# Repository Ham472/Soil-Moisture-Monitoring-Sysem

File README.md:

# Soil-Moisture-Monitoring-Sysem

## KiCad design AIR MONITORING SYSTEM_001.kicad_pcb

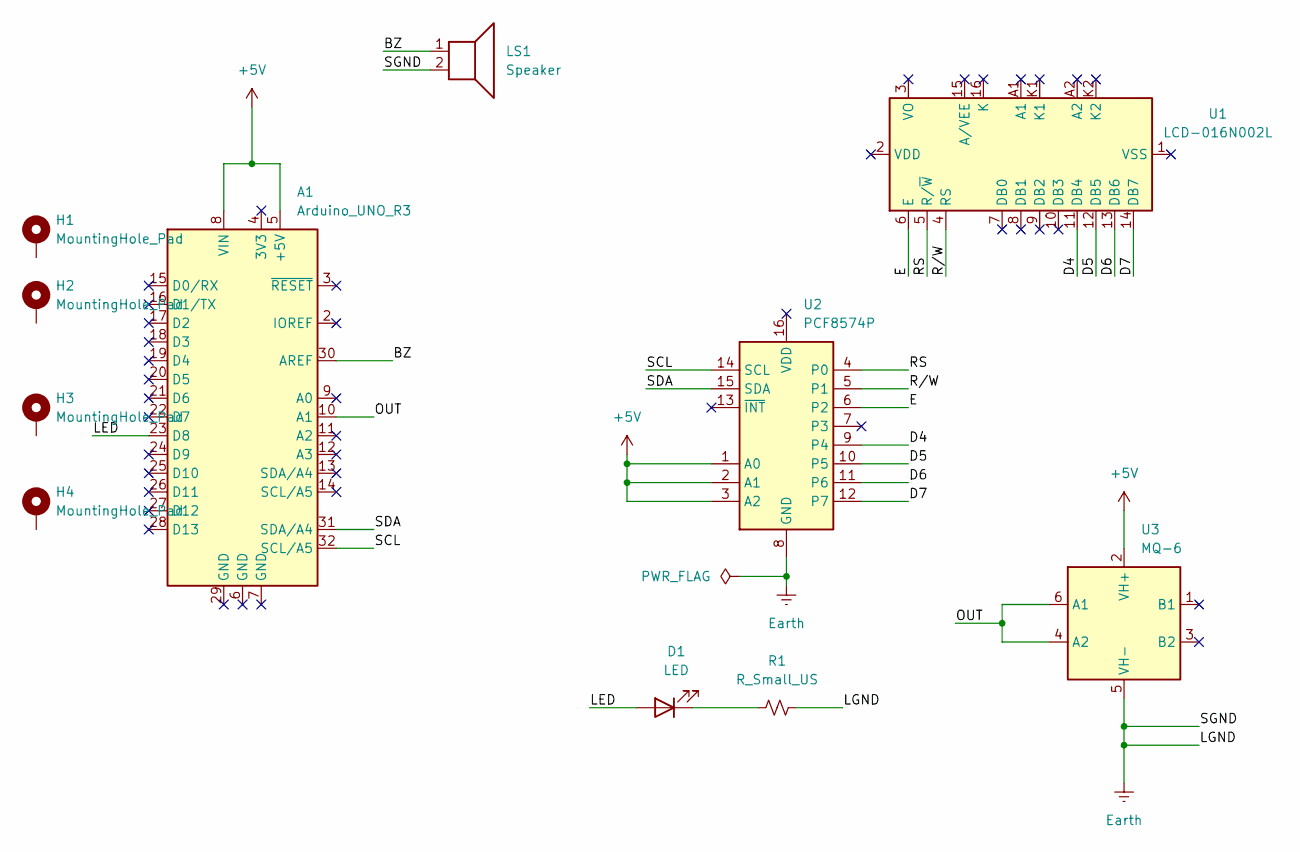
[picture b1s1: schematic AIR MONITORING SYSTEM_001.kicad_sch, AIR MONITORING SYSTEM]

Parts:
A1: Arduino_UNO_R3
D1: LED; LED_D3.0mm_Clear
H1, H2, H3, H4: MountingHole_Pad; MountingHole_2.5mm_Pad
LS1: Speaker; Reverb_BTDR-1H
R1: R_Small_US; R_Axial_DIN0411_L9.9mm_D3.6mm_P7.62mm_Vertical
U1: LCD-016N002L
U2: PCF8574P; DIP-16_W7.62mm
U3: MQ-6

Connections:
+5V: A1.5 (+5V), A1.8 (VIN), U2.1 (A0), U2.2 (A1), U2.3 (A2), U3.2 (VH+)
/BZ: A1.30 (AREF), LS1.1
/D4: U1.11 (DB4), U2.9 (P4)
/D5: U1.12 (DB5), U2.10 (P5)
/D6: U1.13 (DB6), U2.11 (P6)
/D7: U1.14 (DB7), U2.12 (P7)
/E: U1.6 (E), U2.6 (P2)
/LED: A1.23 (D8), D1.2 (A)
/OUT: A1.10 (A1), U3.4 (A2), U3.6 (A1)
/RS: U1.5 (R/~W), U2.4 (P0)
/R/W: U1.4 (RS), U2.5 (P1)
/SCL: A1.32 (SCL/A5), U2.14 (SCL)
/SDA: A1.31 (SDA/A4), U2.15 (SDA)
Earth: LS1.2, R1.2, U2.8 (GND), U3.5 (VH-)
unnamed: D1.1 (K), R1.1

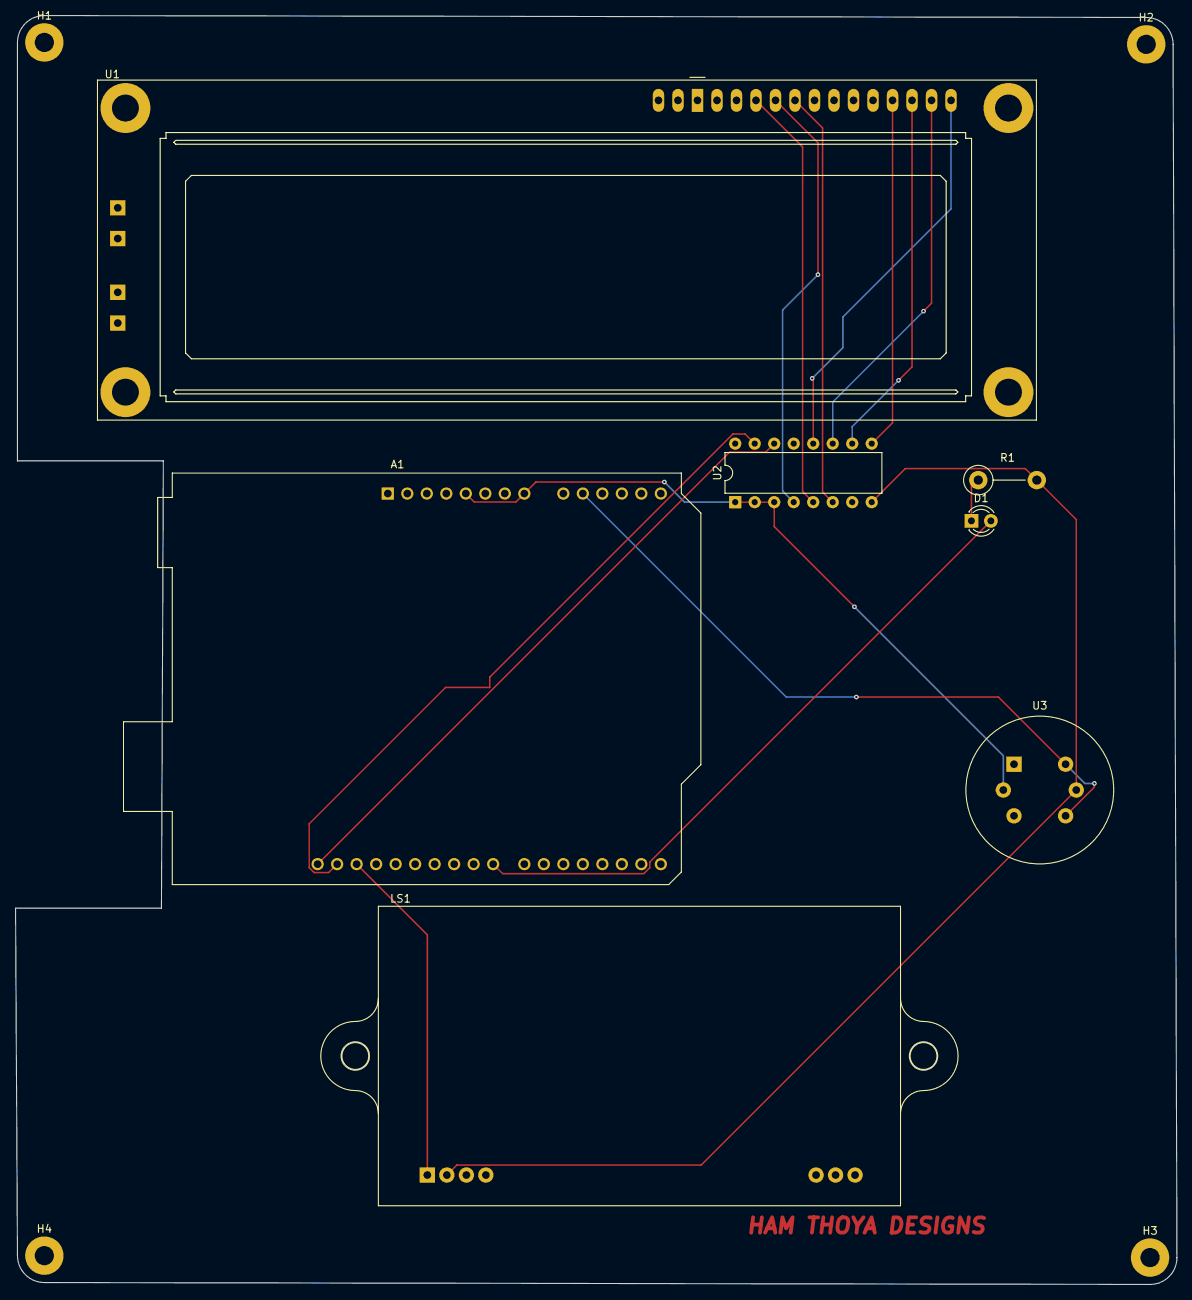
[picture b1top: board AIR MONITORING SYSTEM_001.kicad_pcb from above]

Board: 2 copper layers, 151.2 x 165.2 mm, 11 parts (0 on the bottom side), 15 nets.
